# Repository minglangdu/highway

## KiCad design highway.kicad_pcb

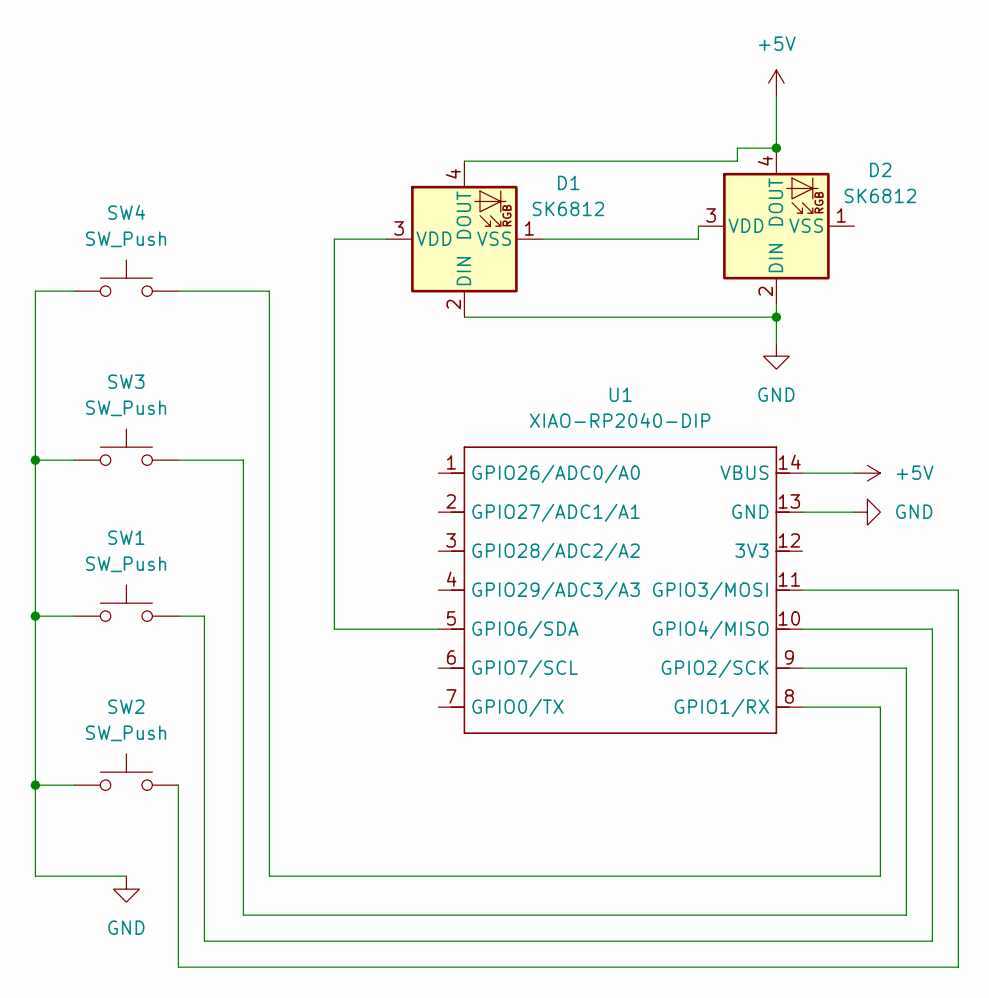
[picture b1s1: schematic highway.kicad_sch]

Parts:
D1, D2: SK6812; LED_SK6812MINI_PLCC4_3.5x3.5mm_P1.75mm
SW1, SW2, SW3, SW4: SW_Push; SW_Cherry_MX_1.00u_PCB
U1: XIAO-RP2040-DIP

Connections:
+5V: D1.4 (DOUT), D2.4 (DOUT), U1.14 (VBUS)
GND: D1.2 (DIN), D2.2 (DIN), SW1.1, SW2.1, SW3.1, SW4.1, U1.13 (GND)
unnamed: D1.3 (VDD), U1.5 (GPIO6/SDA)
unnamed: D1.1 (VSS), D2.3 (VDD)
unnamed: SW4.2, U1.8 (GPIO1/RX)
unnamed: SW3.2, U1.9 (GPIO2/SCK)
unnamed: SW2.2, U1.11 (GPIO3/MOSI)
unnamed: SW1.2, U1.10 (GPIO4/MISO)

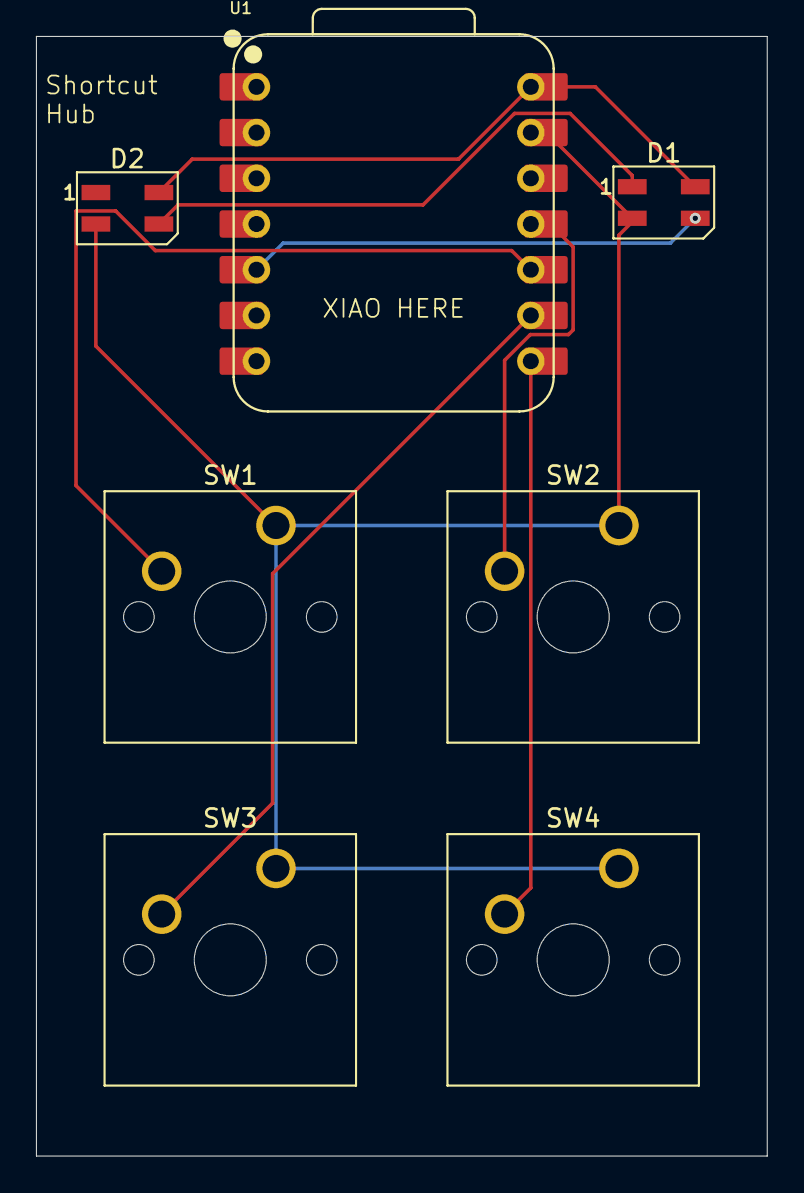
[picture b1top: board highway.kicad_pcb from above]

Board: 2 copper layers, 40.6 x 62.2 mm, 7 parts (0 on the bottom side), 8 nets.

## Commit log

2025-05-23 begin
2025-06-03 add new case
